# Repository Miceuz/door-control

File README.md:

# door-control
An entrance to hackerspace control system

randominis minčių kratinys

 * Du maitinimo blokai - vienas, 5V maitina ESP32 plokštę, kitas, 12V - "purvinąją" pusę
 X* Iš 5V patempti už kojos tranzistorių ir sekti, ar yra 5V maitinimas
 X* Iš 12V per optoporą patempti tranzistorių ir sekti, ar yra 12V maitinimas
 X* RS485 izoliuotas per AD2482/AD2487
 * Išlituoti barrel lizdą įlituoti screw term
 http://www.mouser.com/pdfdocs/Bourns_RS485_AppNote.pdf

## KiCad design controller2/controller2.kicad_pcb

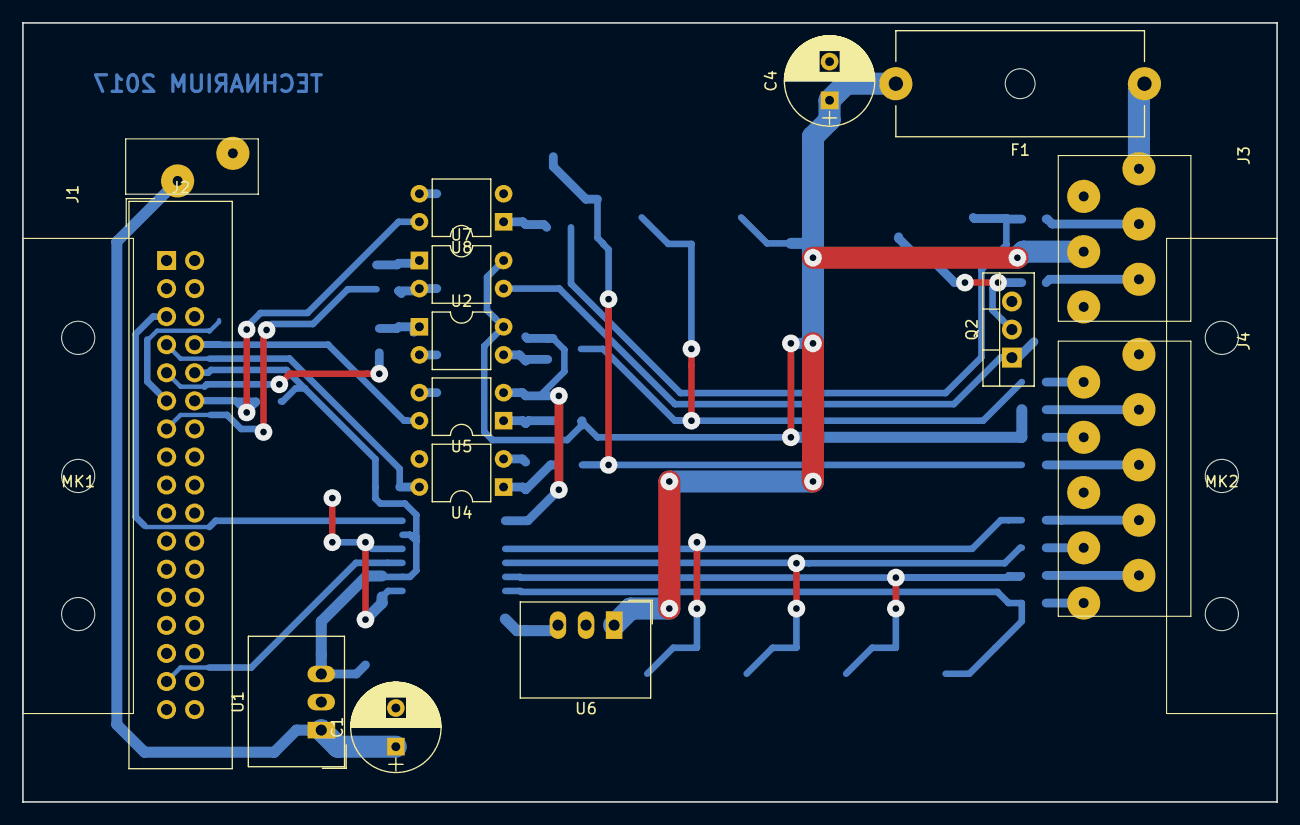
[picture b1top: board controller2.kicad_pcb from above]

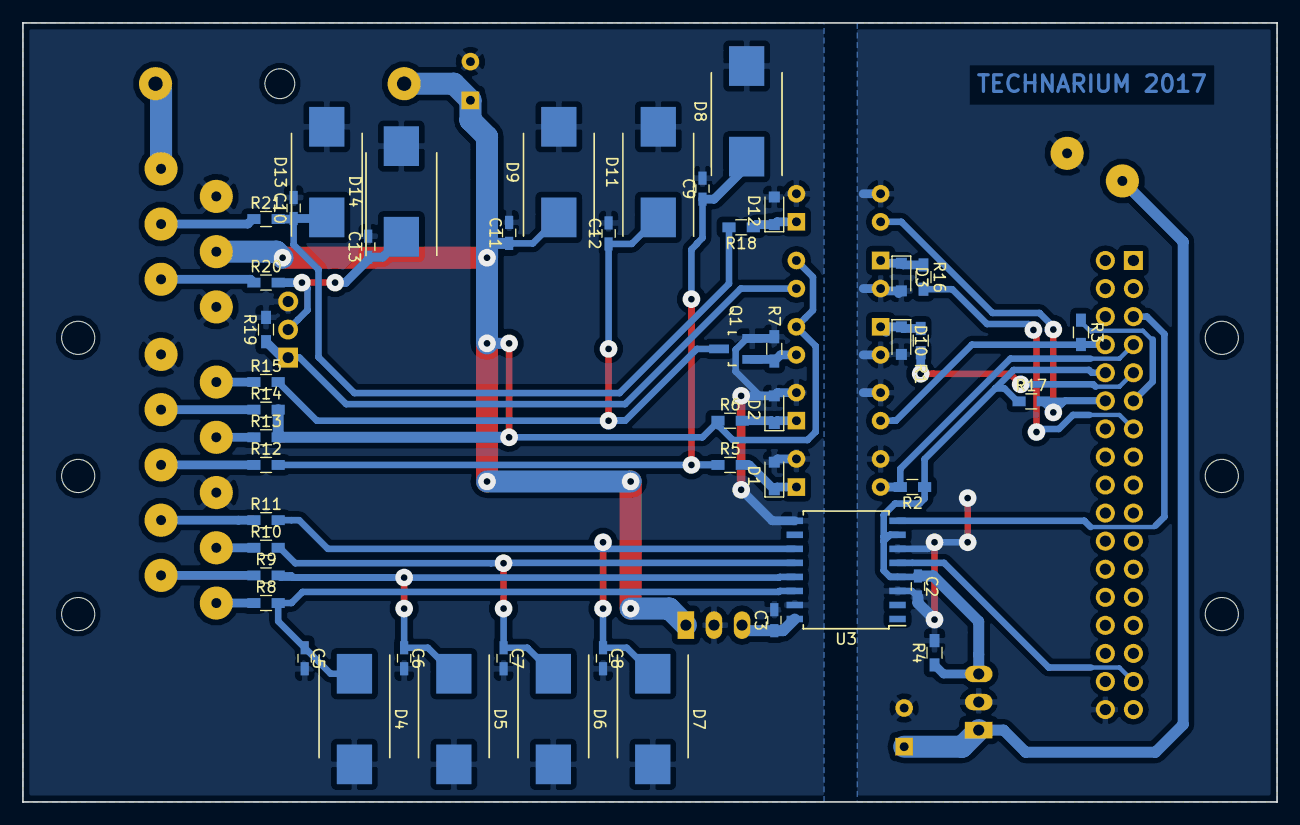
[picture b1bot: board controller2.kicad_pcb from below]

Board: 2 copper layers, 113.5 x 70.5 mm, 65 parts (48 on the bottom side), 40 nets.

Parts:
C1, C4: CP; CP_Radial_D8.0mm_P3.50mm
C2, C3, C5, C6, C7, C8, C9, C10, C11, C12, C13: C; C_0603_HandSoldering
D1, D2, D3, D10, D12: D_Small; D_SOD-323_HandSoldering
D4, D5, D6, D7, D8, D9, D11, D13, D14: SMCJ12CA; DO-214AB_Handsoldering
F1: Fuse; Fuseholder5x20_horiz_open_Schurter_0031_8201
J1: 5V_IN; TerminalBlock_WAGO-205_2pol
J2: Conn_02x17_Odd_Even; IDC-Header_2x17_Pitch2.54mm_Straight
J3: Conn_01x06; TerminalBlock_WAGO-205_10pol
J4: Conn_01x10; TerminalBlock_WAGO-205_10pol
MK1, MK2: Mounting_Hole; DIN_CLIP
Q1: Q_NMOS_GSD; SOT-23_Handsoldering
Q2: Q_NMOS_GSD; TO-220-3_Vertical
R1, R2, R3, R4, R5, R6, R7, R16, R17, R18, R19: R; R_0603_HandSoldering
R8, R9, R10, R11, R12, R13, R14, R15, R20, R21: R_Small; R_0603_HandSoldering
U1, U6: R-78E3.3-0.5; DCDC-Conv_RECOM_R-78E-0.5
U2, U4, U5, U7, U8: TLP222A; DIP-4_W7.62mm
U3: ADM2482; SOIC-16W_7.5x10.3mm_Pitch1.27mm

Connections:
+3V3: C2.1, J2.10, R2.1, R4.1, R17.1, U1.3, U3.4, U3.7
/AUX_IN: C10.1, D13.1, R18.2, R21.2
/AUX_IN_ISO: J2.12, R17.2, U8.4
/AUX_OUT: C13.1, D14.1, Q2.2, R20.2
/AUX_OUT_ISO: J2.13, R16.2
/BUZZ_ISO: J2.9, R1.2
/BUZZ_LED: C12.1, D11.1, Q1.3, R15.2
/RxD: J2.31, U3.5
/SWITCH: C9.1, D8.1, R5.1, R12.2
/TxD: J2.5, U3.8
/VCC_TEST: J2.11, R3.1
/~SWITCH_ISO: J2.7, R2.2, U4.4
/~VCC_GOOD: J2.8, R3.2, U5.4
GND: C1.2, C2.2, D3.2, D10.2, J1.2, J2.34, R4.2, U1.2, U2.2, U3.3, U3.6, U4.3, U5.3, U7.2, U8.3
GNDD: C3.2, C4.2, C5.2, C6.2, C7.2, C8.2, C9.2, C10.2, C11.2, C12.2, C13.2, D1.2, D2.2, D4.2, D5.2, D6.2, D7.2, D8.2, D9.2, D11.2, D12.2, D13.2, D14.2, J3.2, J3.6, J4.1, J4.6, Q1.2, Q2.3, R7.2, R19.2, U3.9, U3.15, U4.2, U5.2, U6.2, U8.2
unnamed: C1.1, J1.1, U1.1
unnamed: C3.1, U3.16, U6.3
unnamed: C5.1, D4.1, R8.2, U3.14
unnamed: C6.1, D5.1, R9.2, U3.13
unnamed: C7.1, D6.1, R10.2, U3.12
unnamed: C8.1, D7.1, R11.2, U3.11
unnamed: D1.1, R5.2, U4.1
unnamed: D2.1, R6.2, U5.1
unnamed: D3.1, R16.1, U7.1
unnamed: D10.1, R1.1, U2.1
unnamed: D12.1, R18.1, U8.1
unnamed: F1.1, J3.1
unnamed: J3.3, R21.1
unnamed: J3.5, R20.1
unnamed: J4.2, R15.1
unnamed: J4.3, R14.1
unnamed: J4.4, R13.1
unnamed: J4.5, R12.1
unnamed: J4.7, R11.1
unnamed: J4.8, R10.1
unnamed: J4.9, R9.1
unnamed: J4.10, R8.1
unnamed: Q1.1, R7.1, U2.3
unnamed: Q2.1, R19.1, U7.3
VCC: C4.1, C11.1, D9.1, F1.2, J3.4, R6.1, R13.2, R14.2, U2.4, U6.1, U7.4

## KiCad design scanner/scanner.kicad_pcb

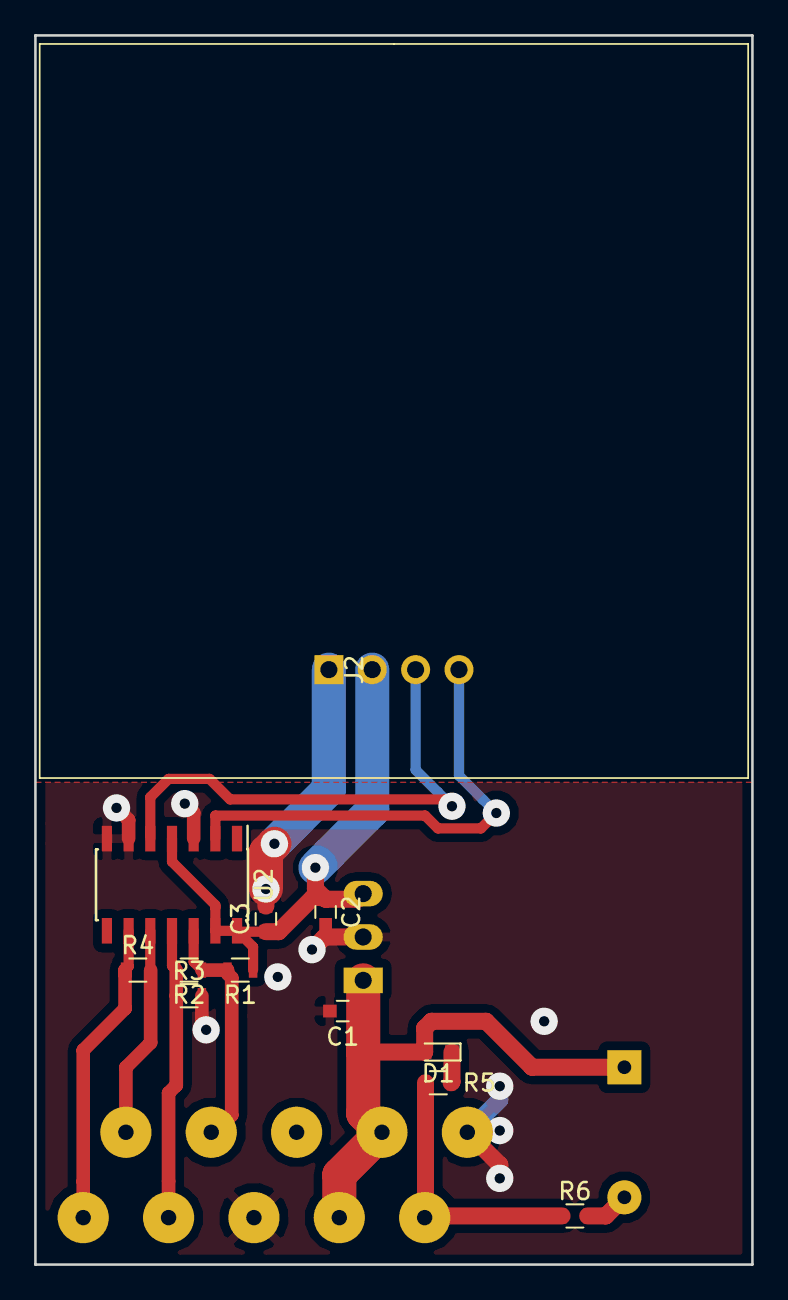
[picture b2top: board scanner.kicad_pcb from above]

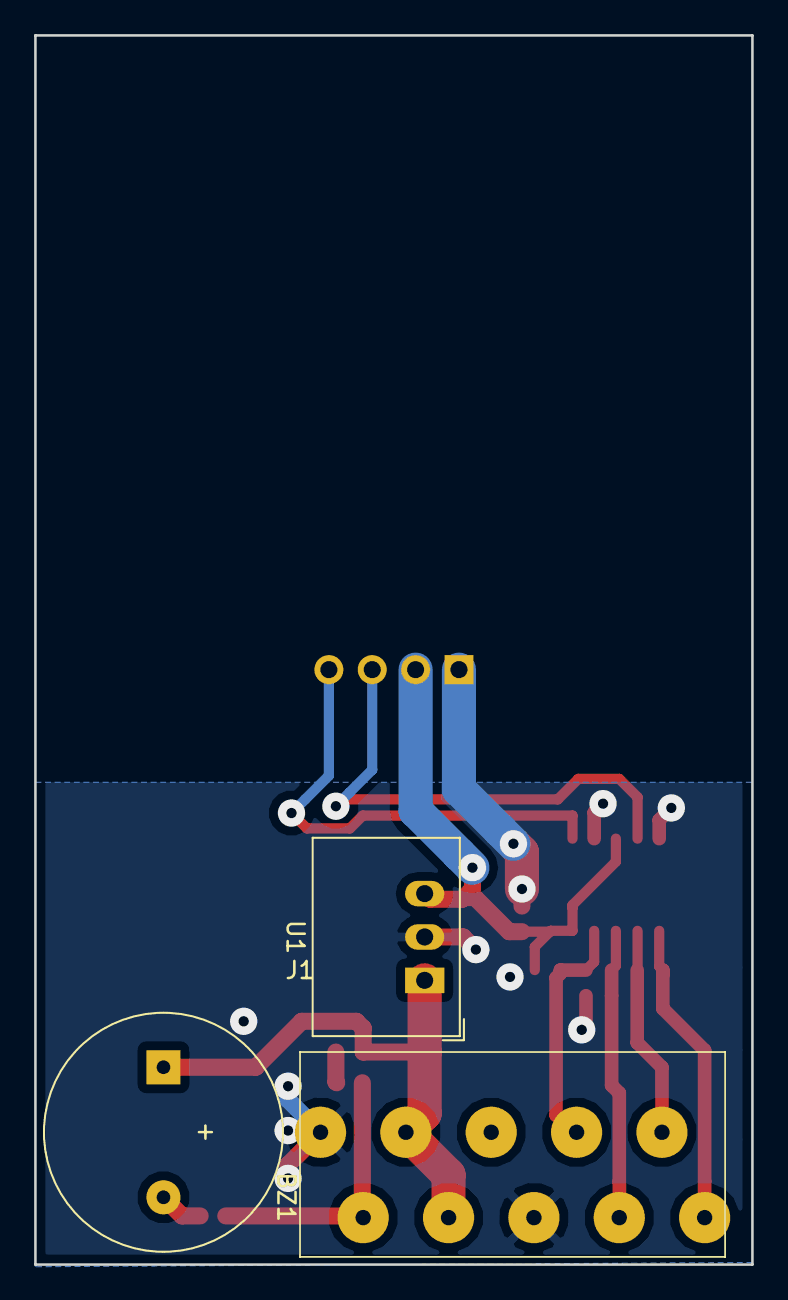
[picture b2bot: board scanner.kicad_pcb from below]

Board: 2 copper layers, 42.0 x 72.0 mm, 15 parts (3 on the bottom side), 12 nets.

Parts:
BZ1: Buzzer; Buzzer_12x9.5RM7.6
C1, C2, C3: 1u; C_0603
D1: LED; LED_0603
J1: Conn_01x10; TerminalBlock_WAGO-804_RM5mm_10pol
J2: Conn_01x04; Pin_Header_Straight_1x04_Pitch2.54mm
R1, R2, R3, R4: R_Small; R_0603
R5, R6: R_0603
U1: R-783.3-0.5; DCDC-Conv_RECOM_R-78E-0.5
U2: ADM3491; SOIC-14_3.9x8.7mm_Pitch1.27mm

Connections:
+3V3: C2.1, C3.1, J2.2, R1.1, U1.3, U2.4, U2.8, U2.13, U2.14
/RXD: J2.4, U2.2
/TXD: J2.3, U2.5
GND: C1.2, C2.2, C3.2, J1.1, J1.6, J2.1, R3.2, U1.2, U2.3, U2.6, U2.7
unnamed: BZ1.2, R6.2
unnamed: D1.1, R5.2
unnamed: J1.2, R5.1, R6.1
unnamed: J1.7, R1.2, R2.1, U2.12
unnamed: J1.8, R2.2, R3.1, U2.11
unnamed: J1.9, R4.2, U2.10
unnamed: J1.10, R4.1, U2.9
VCC: BZ1.1, C1.1, D1.2, J1.3, J1.4, U1.1

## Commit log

2017-01-06 Initial commit. Basic schematics of controller are done
2017-01-06 Move controller related stuff to a separate folder
2017-12-07 Add the most recent stuff - scanner and the new interface board
2017-12-07 Add some 3d models
2017-12-07 Ignore some back files
2017-12-07 Add readme file
2017-12-14 No commit no cry. Controller IO isolation board is ready for manufacturing
2017-12-18 Remove some old stuff
